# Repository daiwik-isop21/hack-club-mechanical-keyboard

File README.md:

# hack-club-mechanical-keyboard
i  will be making a mechanical keybord from scratch with help of hack club providing all the funding i will record all the steps here

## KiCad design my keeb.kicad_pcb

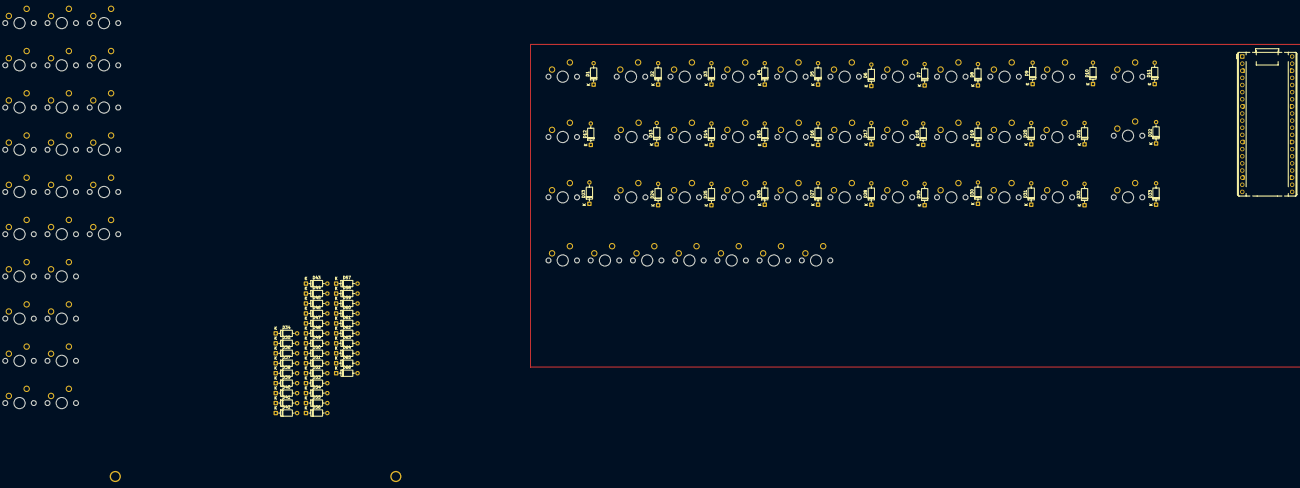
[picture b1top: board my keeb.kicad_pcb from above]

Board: 2 copper layers, 134 parts (0 on the bottom side), 83 nets, no tracks yet.

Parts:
A1: RaspberryPi_Pico; RaspberryPi_Pico_Common_THT
D1, D2, D3, D4, D5, D6, D7, D8, D9, D10, D11, D12, D13, D14, D15, D16, D17, D18, D19, D20, D21, D22, D23, D24, D25, D26, D27, D28, D29, D30, D31, D32, D33, D34, D35, D36, D37, D38, D39, D40, D41, D42, D43, D44, D45, D46, D47, D48, D49, D50, D51, D52, D53, D54, D55, D56, D57, D58, D59, D60, D61, D62, D63, D64, D65, D66: 1N4148; D_DO-35_SOD27_P7.62mm_Horizontal
S1: MX_stab; STAB_MX_P_6.25u
SW1, SW2, SW3, SW4, SW5, SW6, SW7, SW8, SW9, SW10, SW11, SW12, SW13, SW14, SW15, SW16, SW17, SW18, SW19, SW20, SW21, SW22, SW23, SW24, SW25, SW26, SW27, SW28, SW29, SW30, SW31, SW32, SW33, SW34, SW35, SW36, SW37, SW38, SW39, SW40, SW41, SW42, SW43, SW44, SW45, SW46, SW47, SW48, SW49, SW50, SW51, SW52, SW53, SW54, SW55, SW56, SW57, SW58, SW59, SW60, SW61, SW62, SW63, SW64, SW65, SW66: SW_Push; SW_MX_1u

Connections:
/col 1: A1.9 (GPIO6), SW1.1, SW12.1, SW23.1, SW34.1, SW45.1, SW58.1
/col 2: A1.10 (GPIO7), SW2.1, SW13.1, SW24.1, SW35.1, SW46.1, SW56.1
/col 3: A1.11 (GPIO8), SW3.1, SW14.1, SW25.1, SW36.1, SW47.1, SW59.1
/col 4: A1.12 (GPIO9), SW4.1, SW15.1, SW26.1, SW37.1, SW48.1, SW60.1
/col 5: A1.14 (GPIO10), SW5.1, SW16.1, SW27.1, SW38.1, SW49.1, SW61.1
/col 6: A1.15 (GPIO11), SW6.1, SW17.1, SW28.1, SW39.1, SW50.1, SW62.1
/col 7: A1.16 (GPIO12), SW7.1, SW18.1, SW29.1, SW40.1, SW51.1, SW63.1
/col 8: A1.17 (GPIO13), SW8.1, SW19.1, SW30.1, SW41.1, SW52.1, SW64.1
/col 9: A1.19 (GPIO14), SW9.1, SW20.1, SW31.1, SW42.1, SW53.1, SW65.1
/col 10: A1.20 (GPIO15), SW10.1, SW21.1, SW32.1, SW43.1, SW54.1, SW66.1
/col 11: A1.21 (GPIO16), SW11.1, SW22.1, SW33.1, SW44.1, SW55.1, SW57.1
/row 1: A1.1 (GPIO0), D1.1 (K), D2.1 (K), D3.1 (K), D4.1 (K), D5.1 (K), D6.1 (K), D7.1 (K), D8.1 (K), D9.1 (K), D10.1 (K), D11.1 (K)
/row 2: A1.2 (GPIO1), D12.1 (K), D13.1 (K), D14.1 (K), D15.1 (K), D16.1 (K), D17.1 (K), D18.1 (K), D19.1 (K), D20.1 (K), D21.1 (K), D22.1 (K)
/row 3: A1.4 (GPIO2), D23.1 (K), D24.1 (K), D25.1 (K), D26.1 (K), D27.1 (K), D28.1 (K), D29.1 (K), D30.1 (K), D31.1 (K), D32.1 (K), D33.1 (K)
/row 4: A1.5 (GPIO3), D34.1 (K), D35.1 (K), D36.1 (K), D37.1 (K), D38.1 (K), D39.1 (K), D40.1 (K), D41.1 (K), D42.1 (K), D43.1 (K), D44.1 (K)
/row 5: A1.6 (GPIO4), D45.1 (K), D46.1 (K), D47.1 (K), D48.1 (K), D49.1 (K), D50.1 (K), D51.1 (K), D52.1 (K), D53.1 (K), D54.1 (K), D55.1 (K)
/row 6: A1.7 (GPIO5), D56.1 (K), D57.1 (K), D58.1 (K), D59.1 (K), D60.1 (K), D61.1 (K), D62.1 (K), D63.1 (K), D64.1 (K), D65.1 (K), D66.1 (K)
unnamed: D1.2 (A), SW3.2
unnamed: D2.2 (A), SW4.2
unnamed: D3.2 (A), SW5.2
unnamed: D4.2 (A), SW6.2
unnamed: D5.2 (A), SW7.2
unnamed: D6.2 (A), SW8.2
unnamed: D7.2 (A), SW11.2
unnamed: D8.2 (A), SW1.2
unnamed: D9.2 (A), SW2.2
unnamed: D10.2 (A), SW9.2
unnamed: D11.2 (A), SW10.2
unnamed: D12.2 (A), SW12.2
unnamed: D13.2 (A), SW13.2
unnamed: D14.2 (A), SW14.2
unnamed: D15.2 (A), SW17.2
unnamed: D16.2 (A), SW18.2
unnamed: D17.2 (A), SW19.2
unnamed: D18.2 (A), SW20.2
unnamed: D19.2 (A), SW21.2
unnamed: D20.2 (A), SW22.2
unnamed: D21.2 (A), SW15.2
unnamed: D22.2 (A), SW16.2
unnamed: D23.2 (A), SW23.2
unnamed: D24.2 (A), SW24.2
unnamed: D25.2 (A), SW25.2
unnamed: D26.2 (A), SW26.2
unnamed: D27.2 (A), SW27.2
unnamed: D28.2 (A), SW28.2
unnamed: D29.2 (A), SW29.2
unnamed: D30.2 (A), SW30.2
unnamed: D31.2 (A), SW31.2
unnamed: D32.2 (A), SW32.2
unnamed: D33.2 (A), SW33.2
unnamed: D34.2 (A), SW34.2
unnamed: D35.2 (A), SW35.2
unnamed: D36.2 (A), SW36.2
unnamed: D37.2 (A), SW37.2
unnamed: D38.2 (A), SW38.2
unnamed: D39.2 (A), SW39.2
unnamed: D40.2 (A), SW40.2
unnamed: D41.2 (A), SW41.2
unnamed: D42.2 (A), SW42.2
unnamed: D43.2 (A), SW43.2
unnamed: D44.2 (A), SW44.2
unnamed: D45.2 (A), SW46.2
unnamed: D46.2 (A), SW47.2
unnamed: D47.2 (A), SW48.2
unnamed: D48.2 (A), SW49.2
unnamed: D49.2 (A), SW50.2
unnamed: D50.2 (A), SW51.2
unnamed: D51.2 (A), SW52.2
unnamed: D52.2 (A), SW53.2
unnamed: D53.2 (A), SW54.2
unnamed: D54.2 (A), SW55.2
unnamed: D55.2 (A), SW45.2
unnamed: D56.2 (A), SW56.2
unnamed: D57.2 (A), SW57.2
unnamed: D58.2 (A), SW58.2
unnamed: D59.2 (A), SW59.2
unnamed: D60.2 (A), SW60.2
unnamed: D61.2 (A), SW61.2
unnamed: D62.2 (A), SW62.2
unnamed: D63.2 (A), SW63.2
unnamed: D64.2 (A), SW64.2
unnamed: D65.2 (A), SW65.2
unnamed: D66.2 (A), SW66.2
